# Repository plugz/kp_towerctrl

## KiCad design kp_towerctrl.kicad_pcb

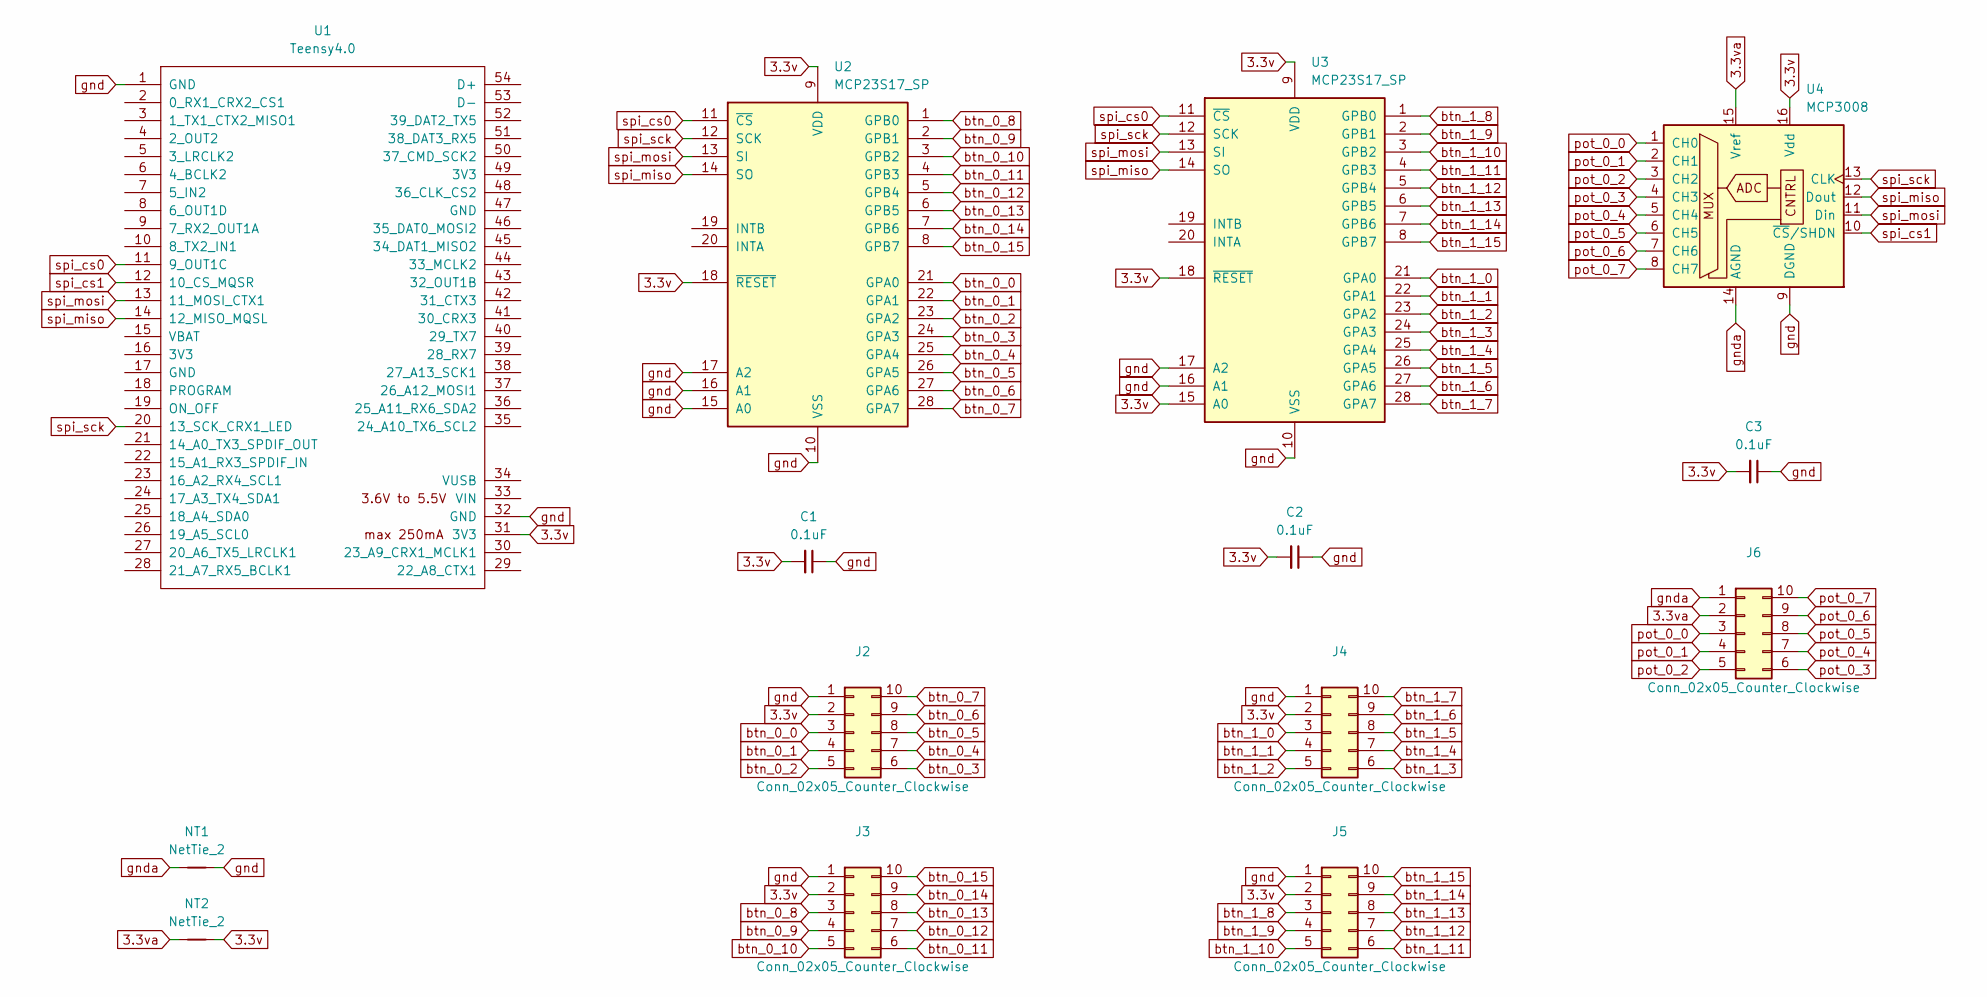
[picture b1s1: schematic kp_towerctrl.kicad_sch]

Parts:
C1, C2, C3: 0.1uF; C_Disc_D7.0mm_W2.5mm_P5.00mm
J2, J3, J4, J5, J6: Conn_02x05_Counter_Clockwise; IDC-Header_2x05_P2.54mm_Vertical
NT1, NT2: NetTie_2; NetTie-2_THT_Pad1.0mm
U1: Teensy4.0; Teensy40_SMT
U2, U3: MCP23S17_SP; DIP-28_W7.62mm
U4: MCP3008; DIP-16_W7.62mm

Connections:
3.3v: C1.2, C2.2, C3.2, J2.2, J3.2, J4.2, J5.2, NT2.2, U1.31 (3V3), U2.9 (VDD), U2.18 (~RESET), U3.9 (VDD), U3.15 (A0), U3.18 (~RESET), U4.16 (Vdd)
3.3va: J6.2, NT2.1, U4.15 (Vref)
btn_0_0: J2.3, U2.21 (GPA0)
btn_0_1: J2.4, U2.22 (GPA1)
btn_0_2: J2.5, U2.23 (GPA2)
btn_0_3: J2.6, U2.24 (GPA3)
btn_0_4: J2.7, U2.25 (GPA4)
btn_0_5: J2.8, U2.26 (GPA5)
btn_0_6: J2.9, U2.27 (GPA6)
btn_0_7: J2.10, U2.28 (GPA7)
btn_0_8: J3.3, U2.1 (GPB0)
btn_0_9: J3.4, U2.2 (GPB1)
btn_0_10: J3.5, U2.3 (GPB2)
btn_0_11: J3.6, U2.4 (GPB3)
btn_0_12: J3.7, U2.5 (GPB4)
btn_0_13: J3.8, U2.6 (GPB5)
btn_0_14: J3.9, U2.7 (GPB6)
btn_0_15: J3.10, U2.8 (GPB7)
btn_1_0: J4.3, U3.21 (GPA0)
btn_1_1: J4.4, U3.22 (GPA1)
btn_1_2: J4.5, U3.23 (GPA2)
btn_1_3: J4.6, U3.24 (GPA3)
btn_1_4: J4.7, U3.25 (GPA4)
btn_1_5: J4.8, U3.26 (GPA5)
btn_1_6: J4.9, U3.27 (GPA6)
btn_1_7: J4.10, U3.28 (GPA7)
btn_1_8: J5.3, U3.1 (GPB0)
btn_1_9: J5.4, U3.2 (GPB1)
btn_1_10: J5.5, U3.3 (GPB2)
btn_1_11: J5.6, U3.4 (GPB3)
btn_1_12: J5.7, U3.5 (GPB4)
btn_1_13: J5.8, U3.6 (GPB5)
btn_1_14: J5.9, U3.7 (GPB6)
btn_1_15: J5.10, U3.8 (GPB7)
gnd: C1.1, C2.1, C3.1, J2.1, J3.1, J4.1, J5.1, NT1.2, U1.1 (GND), U1.32 (GND), U2.10 (VSS), U2.15 (A0), U2.16 (A1), U2.17 (A2), U3.10 (VSS), U3.16 (A1), U3.17 (A2), U4.9 (DGND)
gnda: J6.1, NT1.1, U4.14 (AGND)
pot_0_0: J6.3, U4.1 (CH0)
pot_0_1: J6.4, U4.2 (CH1)
pot_0_2: J6.5, U4.3 (CH2)
pot_0_3: J6.6, U4.4 (CH3)
pot_0_4: J6.7, U4.5 (CH4)
pot_0_5: J6.8, U4.6 (CH5)
pot_0_6: J6.9, U4.7 (CH6)
pot_0_7: J6.10, U4.8 (CH7)
spi_cs0: U1.11 (9_OUT1C), U2.11 (~CS), U3.11 (~CS)
spi_cs1: U1.12 (10_CS_MQSR), U4.10 (~CS/SHDN)
spi_miso: U1.14 (12_MISO_MQSL), U2.14 (SO), U3.14 (SO), U4.12 (Dout)
spi_mosi: U1.13 (11_MOSI_CTX1), U2.13 (SI), U3.13 (SI), U4.11 (Din)
spi_sck: U1.20 (13_SCK_CRX1_LED), U2.12 (SCK), U3.12 (SCK), U4.13 (CLK)

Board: 2 copper layers, 14 parts (0 on the bottom side), 49 nets, no tracks yet.

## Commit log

2023-09-02 init commit
2023-09-02 add startup kicad files
2023-09-04 the whole thing
2023-09-04 connect 3.3v
2026-02-15 update to kicad9
